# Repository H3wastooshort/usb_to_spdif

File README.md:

## Compiling

```
git clone https://github.com/raspberrypi/pico-sdk.git
mkdir build
cmake -B ./build -DCMAKE_BUILD_TYPE=Release -DPICO_EXTRAS_PATH=./firmware/pico-extras/ -DPICO_SDK_PATH=./pico-sdk/ firmware/
cmake --build ./build --config Release
cp build/foxdac/foxdac.uf2 /path/to/RPI-RP2
```

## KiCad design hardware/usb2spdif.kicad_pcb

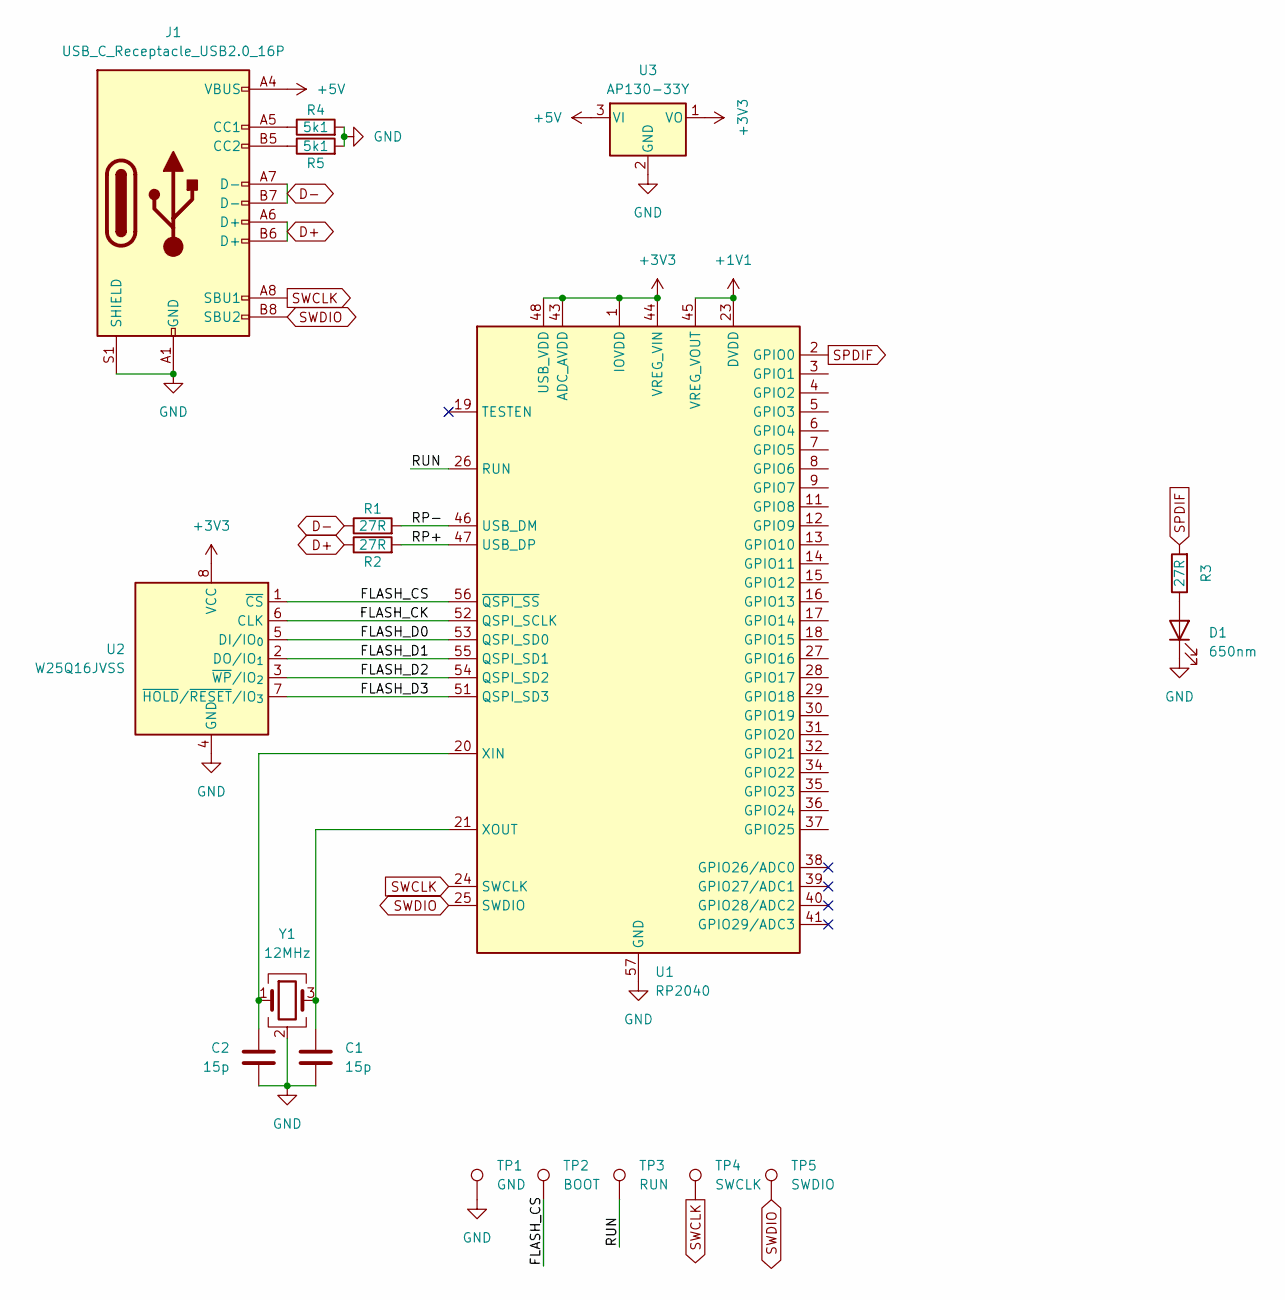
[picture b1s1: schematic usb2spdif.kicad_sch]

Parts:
C1, C2: 15p; C_0603_1608Metric
D1: 650nm; LED_D3.0mm_Horizontal_O1.27mm_Z2.0mm_Clear
J1: USB_C_Receptacle_USB2.0_16P; USB_C_Receptacle_HRO_TYPE-C-31-M-12
R1, R2, R3: 27R; R_0603_1608Metric
R4, R5: 5k1; R_0603_1608Metric
TP1: GND; TestPoint_Pad_D2.0mm
TP2: BOOT; TestPoint_Pad_D2.0mm
TP3: RUN; TestPoint_Pad_D2.0mm
TP4: SWCLK; TestPoint_Pad_D2.0mm
TP5: SWDIO; TestPoint_Pad_D2.0mm
U1: RP2040; QFN-56-1EP_7x7mm_P0.4mm_EP3.2x3.2mm
U2: W25Q16JVSS; SOIC-8_5.3x5.3mm_P1.27mm
U3: AP130-33Y; SOT-89-3
Y1: 12MHz; Crystal_SMD_2016-4Pin_2.0x1.6mm

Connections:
+1V1: U1.23 (DVDD), U1.45 (VREG_VOUT), U1.50 (DVDD)
+3V3: U1.1 (IOVDD), U1.10 (IOVDD), U1.22 (IOVDD), U1.33 (IOVDD), U1.42 (IOVDD), U1.43 (ADC_AVDD), U1.44 (VREG_VIN), U1.48 (USB_VDD), U1.49 (IOVDD), U2.8 (VCC), U3.1 (VO)
+5V: J1.A4 (VBUS), J1.A9 (VBUS), J1.B4 (VBUS), J1.B9 (VBUS), U3.3 (VI)
/FLASH_CK: U1.52 (QSPI_SCLK), U2.6 (CLK)
/FLASH_CS: TP2.1, U1.56 (~QSPI_SS), U2.1 (~CS)
/FLASH_D0: U1.53 (QSPI_SD0), U2.5 (DI/IO_{0})
/FLASH_D1: U1.55 (QSPI_SD1), U2.2 (DO/IO_{1})
/FLASH_D2: U1.54 (QSPI_SD2), U2.3 (~WP/IO_{2})
/FLASH_D3: U1.51 (QSPI_SD3), U2.7 (~HOLD/~RESET/IO_{3})
/RP+: R2.2, U1.47 (USB_DP)
/RP-: R1.2, U1.46 (USB_DM)
/RUN: TP3.1, U1.26 (RUN)
D+: J1.A6 (D+), J1.B6 (D+), R2.1
D-: J1.A7 (D-), J1.B7 (D-), R1.1
GND: C1.2, C2.2, D1.1 (K), J1.A1 (GND), J1.A12 (GND), J1.B1 (GND), J1.B12 (GND), J1.S1 (SHIELD), R4.2, R5.2, TP1.1, U1.57 (GND), U2.4 (GND), U3.2 (GND), Y1.2 (G), Y1.4 (G)
unnamed: D1.2 (A), R3.1
unnamed: J1.A5 (CC1), R4.1
unnamed: J1.B5 (CC2), R5.1
unnamed: C2.1, U1.20 (XIN), Y1.1
unnamed: C1.1, U1.21 (XOUT), Y1.3
SPDIF: R3.2, U1.2 (GPIO0)
SWCLK: J1.A8 (SBU1), TP4.1, U1.24 (SWCLK)
SWDIO: J1.B8 (SBU2), TP5.1, U1.25 (SWDIO)

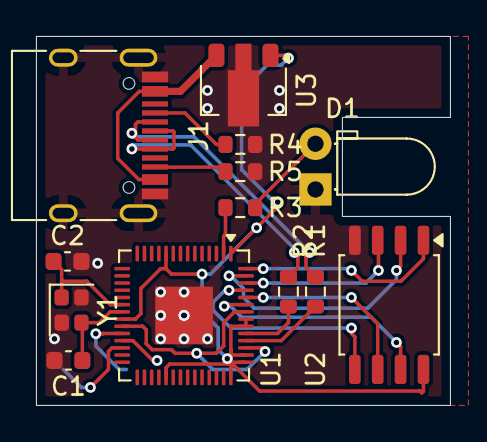
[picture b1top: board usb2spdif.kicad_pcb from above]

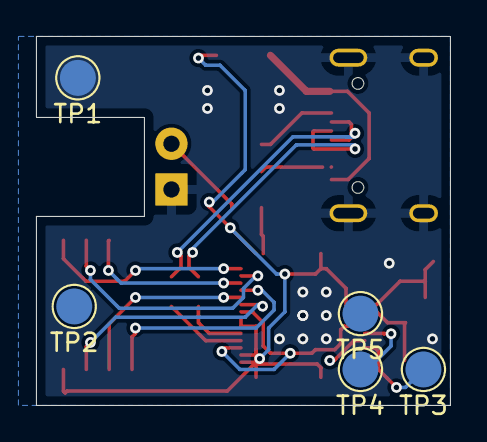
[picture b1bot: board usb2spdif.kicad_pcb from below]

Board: 2 copper layers, 23.0 x 20.5 mm, 18 parts (5 on the bottom side), 23 nets.

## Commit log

2025-08-30 remove FoxDAC hardware
2025-08-30 remove FoxDAC hardware stuff from firmware
2025-08-30 attempt to remove hardware volume control dmesg complains about missing unit
2025-09-09 use unique serial number
2025-09-10 change pins for compat with RP2040-PICO board
2025-09-11 revert volcontrol removal
2025-09-17 v1 pins
2026-01-25 [PCB] add badly routed PCB
2026-01-25 [PCB] minor adjustments
2026-01-25 [PCB] add real toslink TX and S/PDIF coax to schematic
2026-03-23 fix volume control (untested)
2026-03-23 better volume control it was already implemented :facepalm:
2026-03-23 [PCB] forgot to commit that
2026-03-23 remove memcpy that's no longer needed
